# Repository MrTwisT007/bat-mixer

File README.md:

# What's this?
This is a 4-stereo-channel audio mixer I made circa 2018. It's simple design is based on NE5532 opamps.

# What's in it?
The repo contains the KICAD project files for the mixer. I've updated it for KICAD 7.0 (my currently installed version), but I have lost the custom footprints I made at the time. Still, the PCB file is sufficient to reproduce the board.

# Photos

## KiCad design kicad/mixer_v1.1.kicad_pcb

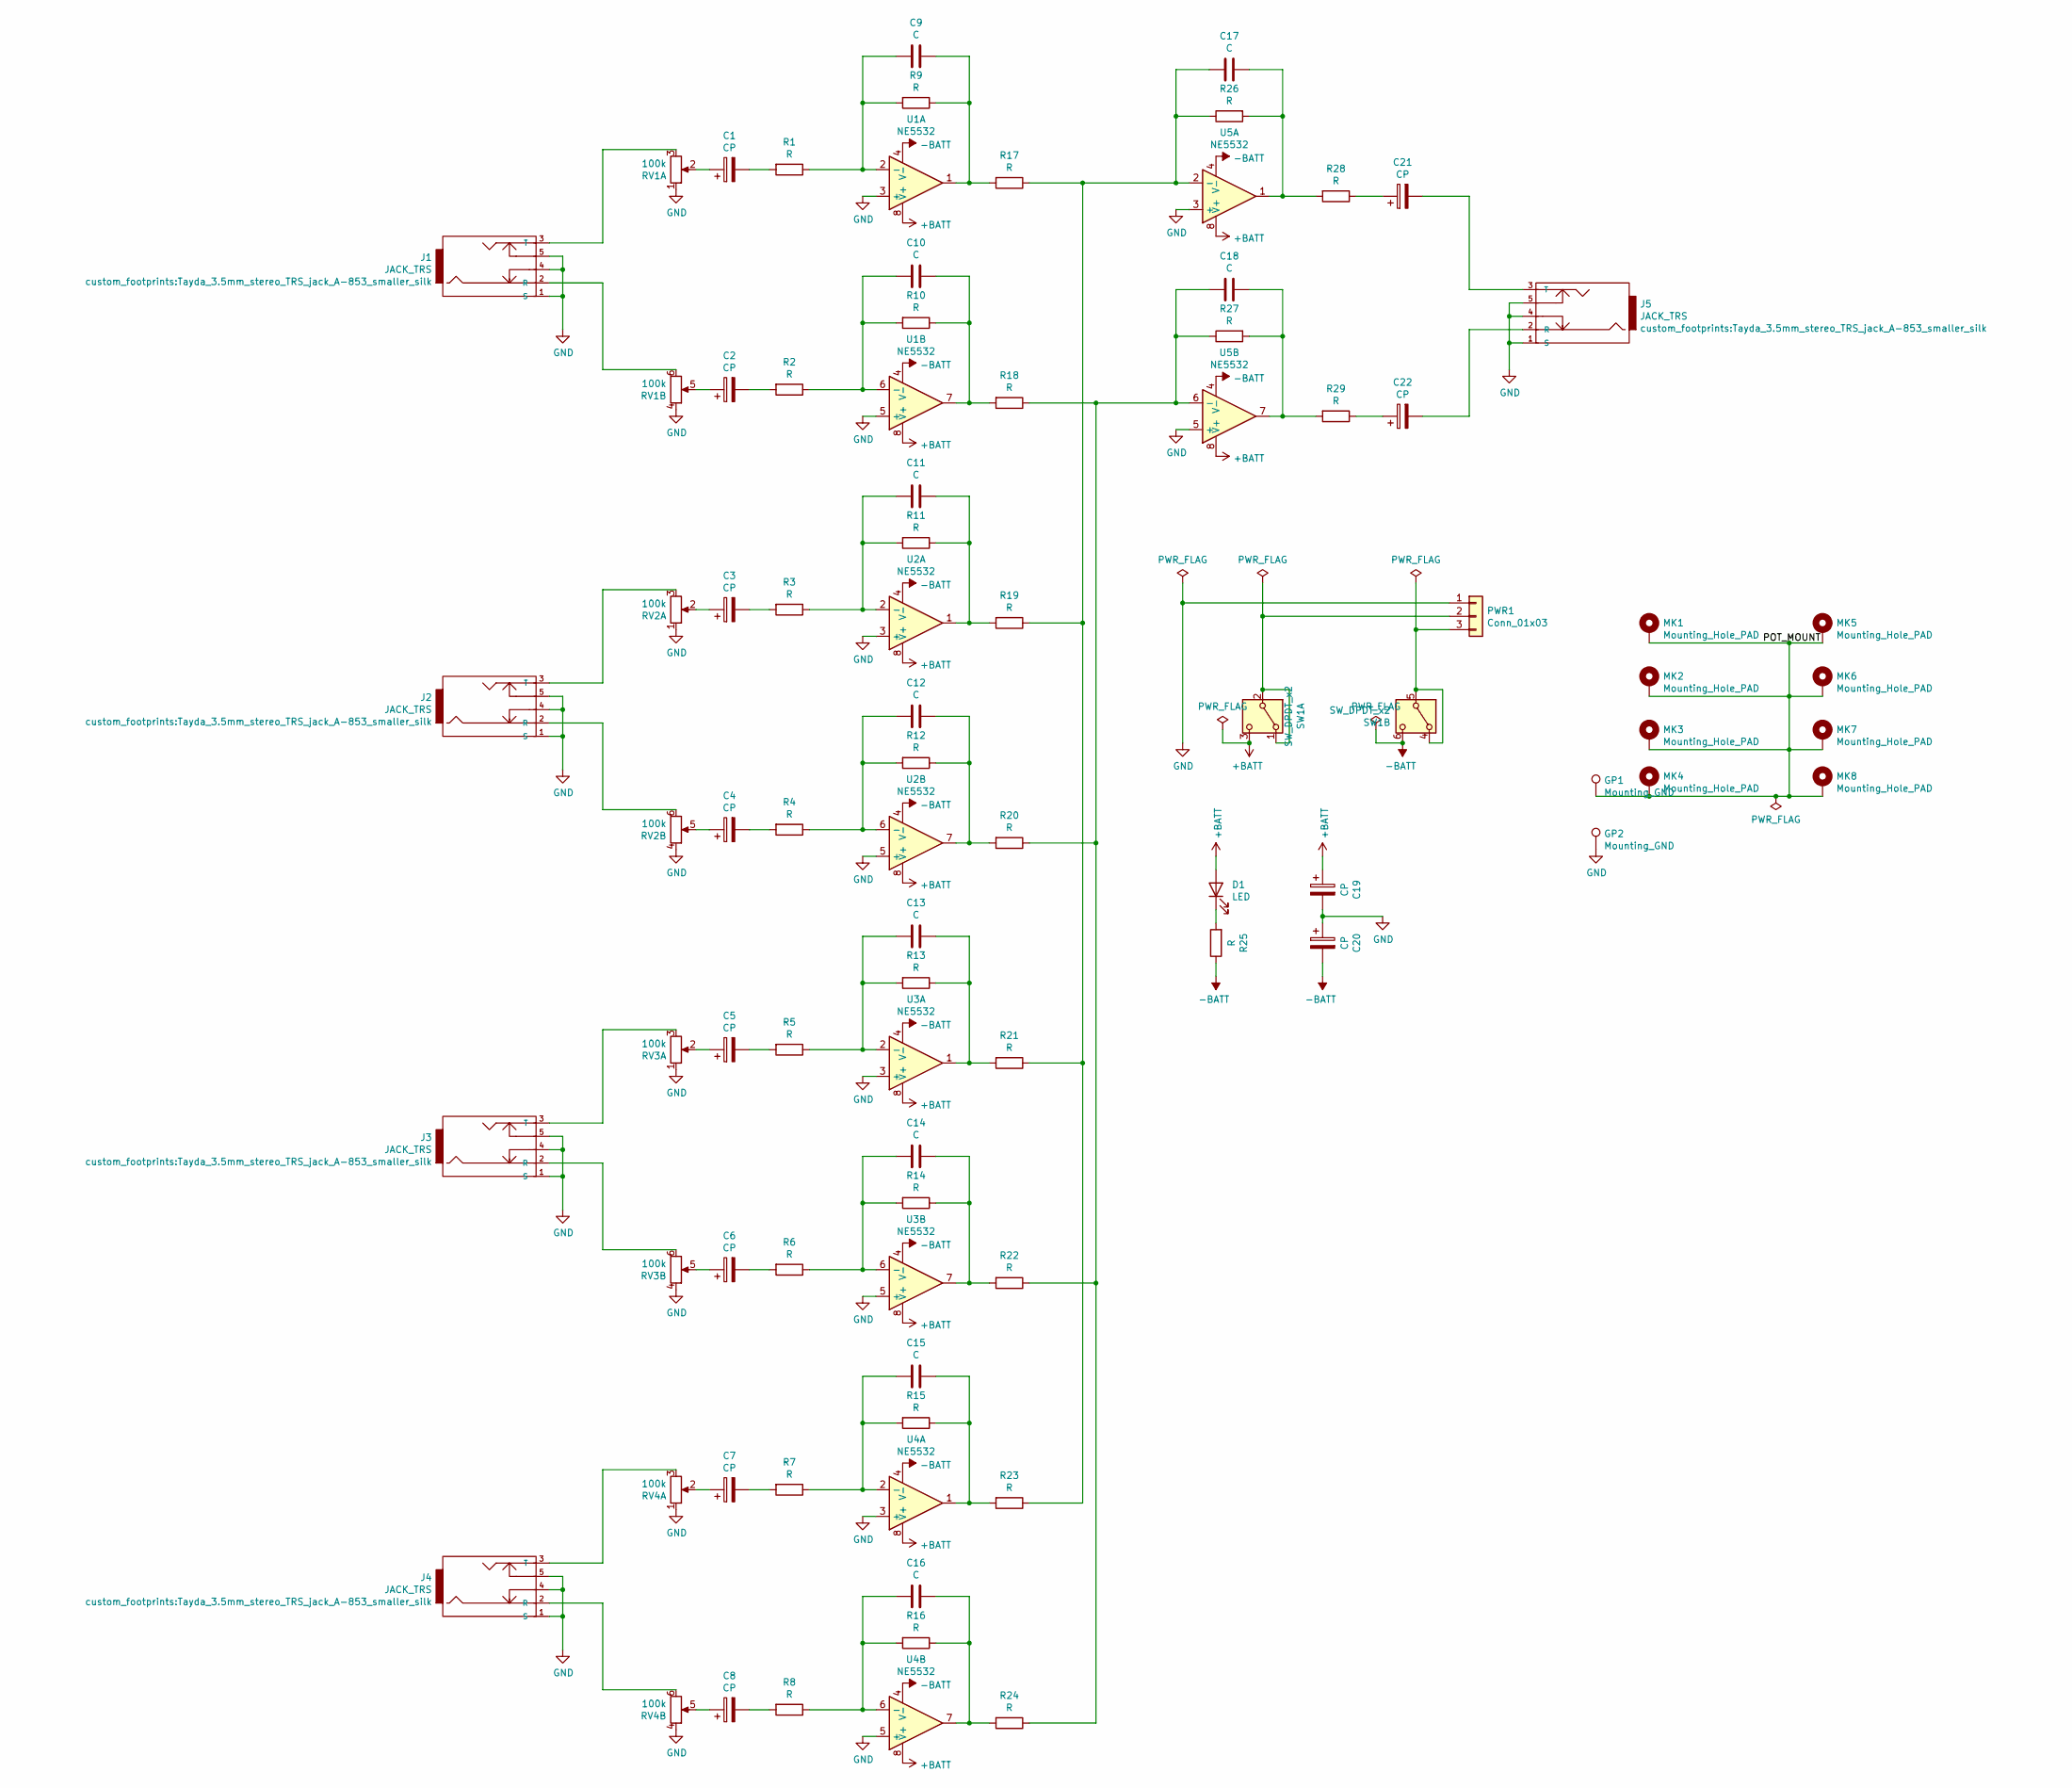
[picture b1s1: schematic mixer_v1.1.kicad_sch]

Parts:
C1, C2, C3, C4, C5, C6, C7, C8, C19, C20, C21, C22: CP; CP_Radial_D5.0mm_P2.50mm
C9, C10, C11, C12, C13, C14, C15, C16, C17, C18: C; C_Disc_D3.0mm_W2.0mm_P2.50mm
D1: LED; LED_D3.0mm
GP1: Mounting_GND; Measurement_Point_Round-SMD-Pad_Small
GP2: Mounting_GND; Test_Point_Keystone_5000-5004_Miniature
J1, J2, J3, J4, J5: JACK_TRS; Tayda_3.5mm_stereo_TRS_jack_A-853_smaller_silk
MK1, MK2, MK3, MK4: Mounting_Hole_PAD; MountingHole_8mm_PAD
MK5, MK6, MK7, MK8: Mounting_Hole_PAD; MountingHole_3.2mm_M3_Pad
PWR1: Conn_01x03; Socket_Strip_Straight_1x03_Pitch2.54mm
R1, R2, R3, R4, R5, R6, R7, R8, R9, R10, R11, R12, R13, R14, R15, R16, R17, R18, R19, R20, R21, R22, R23, R24, R25, R26, R27, R28, R29: R; R_Axial_DIN0207_L6.3mm_D2.5mm_P2.54mm_Vertical
RV1, RV2, RV3, RV4: 100k; Potentiometer_Alps_RK163_Double_Vertical_smaller
SW1: SW_DPDT_x2; Switch_DPDT_6pin
U1, U2, U3, U4, U5: NE5532; DIP-8_W7.62mm_LongPads

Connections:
+BATT: C19.1, D1.2 (A), SW1.3 (C), U1.8 (V+), U2.8 (V+), U3.8 (V+), U4.8 (V+), U5.8 (V+)
-BATT: C20.2, R25.1, SW1.6 (C), U1.4 (V-), U2.4 (V-), U3.4 (V-), U4.4 (V-), U5.4 (V-)
/POT_MOUNT: GP1.1, MK1.1, MK2.1, MK3.1, MK4.1, MK5.1, MK6.1, MK7.1, MK8.1
GND: C19.2, C20.1, GP2.1, J1.1 (S), J1.4, J1.5, J2.1 (S), J2.4, J2.5, J3.1 (S), J3.4, J3.5, J4.1 (S), J4.4, J4.5, J5.1 (S), J5.4, J5.5, PWR1.1, RV1.1, RV1.4, RV2.1, RV2.4, RV3.1, RV3.4, RV4.1, RV4.4, U1.3 (+), U1.5 (+), U2.3 (+), U2.5 (+), U3.3 (+), U3.5 (+), U4.3 (+), U4.5 (+), U5.3 (+), U5.5 (+)
unnamed: C1.1, RV1.2
unnamed: C1.2, R1.2
unnamed: C2.1, RV1.5
unnamed: C2.2, R2.2
unnamed: C3.1, RV2.2
unnamed: C3.2, R3.2
unnamed: C4.1, RV2.5
unnamed: C4.2, R4.2
unnamed: C5.1, RV3.2
unnamed: C5.2, R5.2
unnamed: C6.1, RV3.5
unnamed: C6.2, R6.2
unnamed: C7.1, RV4.2
unnamed: C7.2, R7.2
unnamed: C8.1, RV4.5
unnamed: C8.2, R8.2
unnamed: C9.1, R9.1, R17.2, U1.1
unnamed: C10.1, R10.1, R18.2, U1.7
unnamed: C11.1, R11.1, R19.2, U2.1
unnamed: C12.1, R12.1, R20.2, U2.7
unnamed: C13.1, R13.1, R21.2, U3.1
unnamed: C14.1, R14.1, R22.2, U3.7
unnamed: C15.1, R15.1, R23.2, U4.1
unnamed: C16.1, R16.1, R24.2, U4.7
unnamed: C17.1, R26.2, R28.2, U5.1
unnamed: C18.1, R27.2, R29.2, U5.7
unnamed: C21.1, R28.1
unnamed: C22.1, R29.1
unnamed: D1.1 (K), R25.2
unnamed: J1.2 (R), RV1.6
unnamed: J1.3 (T), RV1.3
unnamed: J2.2 (R), RV2.6
unnamed: J2.3 (T), RV2.3
unnamed: J3.2 (R), RV3.6
unnamed: J3.3 (T), RV3.3
unnamed: J4.2 (R), RV4.6
unnamed: J4.3 (T), RV4.3
unnamed: C22.2, J5.2 (R)
unnamed: C21.2, J5.3 (T)
unnamed: PWR1.2, SW1.1 (A), SW1.2 (B)
unnamed: PWR1.3, SW1.4 (A), SW1.5 (B)
unnamed: C9.2, R1.1, R9.2, U1.2 (-)
unnamed: C10.2, R2.1, R10.2, U1.6 (-)
unnamed: C11.2, R3.1, R11.2, U2.2 (-)
unnamed: C12.2, R4.1, R12.2, U2.6 (-)
unnamed: C13.2, R5.1, R13.2, U3.2 (-)
unnamed: C14.2, R6.1, R14.2, U3.6 (-)
unnamed: C15.2, R7.1, R15.2, U4.2 (-)
unnamed: C16.2, R8.1, R16.2, U4.6 (-)
unnamed: C17.2, R17.1, R19.1, R21.1, R23.1, R26.1, U5.2 (-)
unnamed: C18.2, R18.1, R20.1, R22.1, R24.1, R27.1, U5.6 (-)

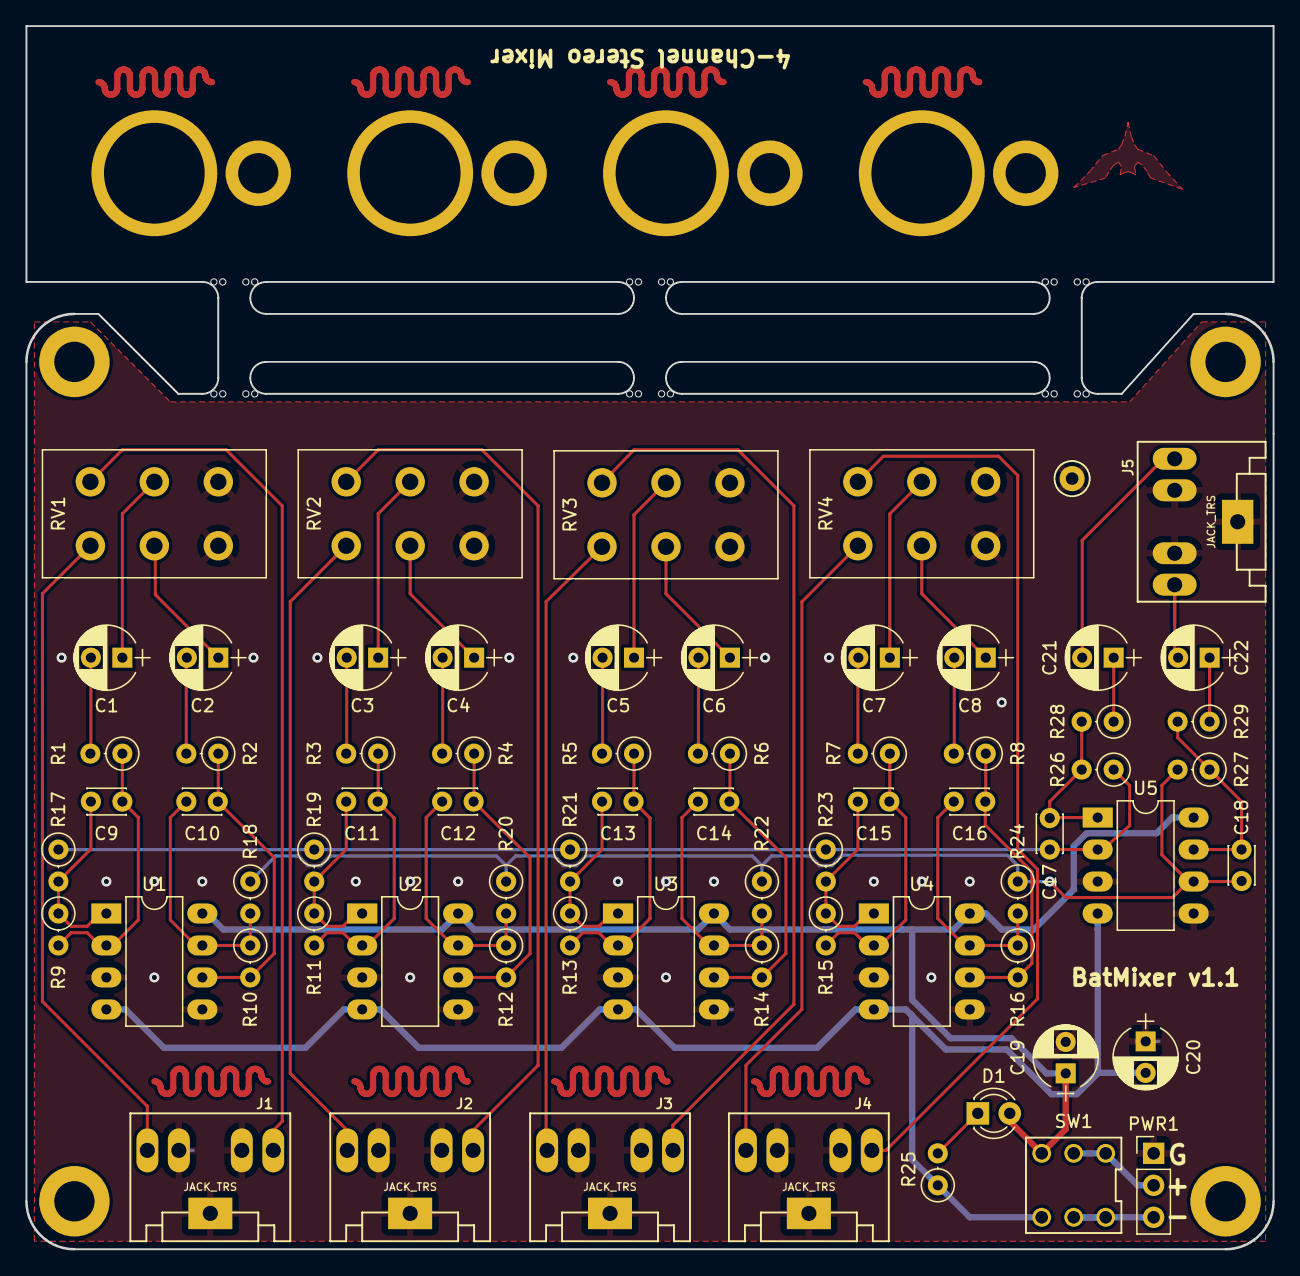
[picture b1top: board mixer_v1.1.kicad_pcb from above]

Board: 2 copper layers, 99.1 x 97.1 mm, 90 parts (0 on the bottom side), 55 nets.

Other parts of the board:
mouse-bite-1mm-slot, mouse-bite-1mm-slot#2, mouse-bite-1mm-slot#3, mouse-bite-1mm-slot#4, mouse-bite-1mm-slot#5, mouse-bite-1mm-slot#6, mouse-bite-1mm-slot#7, mouse-bite-1mm-slot#8, mouse-bite-1mm-slot#9, mouse-bite-1mm-slot#10, mouse-bite-1mm-slot#11, mouse-bite-1mm-slot#12: VAL**; mouse-bite-1mm-line

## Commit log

2026-05-25 Replaced some photos
